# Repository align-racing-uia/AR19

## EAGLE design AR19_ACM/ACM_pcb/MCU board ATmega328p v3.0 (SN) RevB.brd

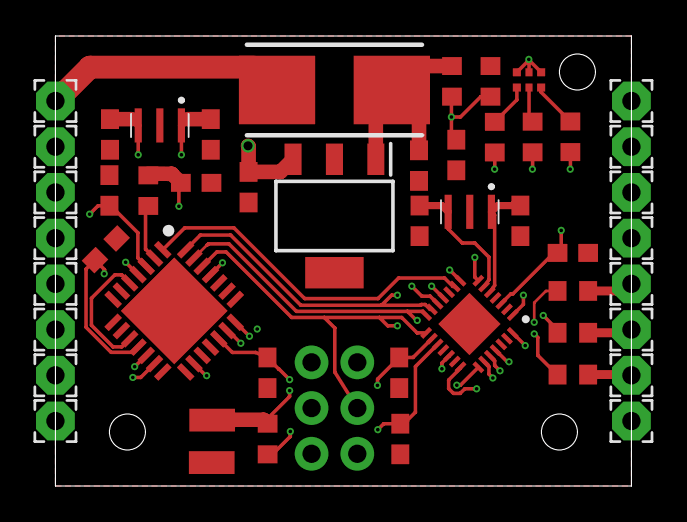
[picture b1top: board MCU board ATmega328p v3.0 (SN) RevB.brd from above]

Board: 4 copper layers, 32.0 x 25.0 mm, 50 parts (0 on the bottom side), 35 nets.

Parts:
5V: 5V_V5; 2,15/1,0
5V1: 5V_H0; 2,15/1,0
12V: 12V_V7; 2,15/1,0
C1, C6, C7, C8, C12, C13, C16, C17: 0.1uF; C0603
C2, C3, C5, C9: 22pF; C0603
C10, C11: 10uF; C0603
CANH: I/O_CANH_V3; 2,15/1,0
CANL: I/O_CANH_V4; 2,15/1,0
FUSE: 0154005.DRT; 0154001.DRT
GND: GND_V6; 2,15/1,0
GND30: GND_V0; 2,15/1,0
I/O_AD0: I/O_AD0_H7; 2,15/1,0
I/O_AD1: I/O_AD1_H6; 2,15/1,0
I/O_ADC2_SDA: I/O_ADC2_SDA_H5; 2,15/1,0
I/O_ADC3_SCL: I/O_ADC3_SCL_H4; 2,15/1,0
IC1: ATMEGA328P-MMH; QFN45P400X400X100-29N
IC2: MIC5239-5.0YS_TR; SOT230P700X170-4N
IC3: MCP25625-E_ML; QFN65P600X600X100-29N
J1: AVR_SPI_PROG_3X2NS; 2X3-NS
LED1: SMLP36RGB2W3R; ROHM-1510-(0604)
MISO: MISO_H3; 2,15/1,0
MOSI: MOSI__H2; 2,15/1,0
PWM0: PWM0_V2; 2,15/1,0
PWM1_INT1: PWM0_INT_V1; 2,15/1,0
R1, R3: 10kOhm; R0603
R2, R6, R7, R8: 200Ohm; R0603
R4: 290Ohm; R0603
R5: 190Ohm; R0603
R9: 3kOhm; R0603
R10: 2kOhm; R0603
RES_PAD1: RES_PAD; SMD1,27-2,54
RES_PAD2: RES_PAD2; SMD1,27-2,54
SCK: SCK_H1; 2,15/1,0
U1, U2: CSTNE16M0V530000R0

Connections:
5V: 5V.1, 5V1.1, C6.1, C7.1, C8.1, C11.1, C12.1, C13.1, C16.1, C17.1, IC1.3, IC1.16, IC1.17, IC2.3, IC3.3, IC3.11, IC3.19, J1.2, LED1.4, LED1.5, LED1.6, R1.1, R3.2
12V_FUSED: C10.1, FUSE.2, IC2.1, R9.2
12V_UNFUSED: 12V.1, FUSE.1
BLUE_LED: IC1.11, R5.1
CANH: CANH.1, IC3.13
CANL: CANL.1, IC3.12
CAN_CS: IC1.9, IC3.1
CAN_INT: IC1.28, IC3.25
CAN_OSC1: C5.1, IC3.21, U1.1
CAN_OSC2: C2.1, IC3.20, U1.3
GND: C1.2, C2.2, C3.2, C5.2, C6.2, C7.2, C8.2, C9.2, C10.2, C11.2, C12.2, C13.2, C16.2, C17.2, GND.1, GND30.1, IC1.4, IC1.18, IC1.29, IC2.2, IC2.4, IC3.14, IC3.15, IC3.17, IC3.18, IC3.22, IC3.29, J1.6, R10.1, RES_PAD2.1, U1.2, U2.2
GREEN_LED: IC1.8, R2.1
I/OAD0: I/O_AD0.1, IC1.22
I/OADC2: I/O_ADC2_SDA.1, IC1.23
I/O_ADC3: I/O_ADC3_SCL.1, IC1.24
I/O_D2_INT: IC1.1, PWM1_INT1.1
MCU_OSC1: C3.1, IC1.5, U2.1
MCU_OSC2: C9.1, IC1.6, U2.3
MISO: IC1.14, IC3.27, J1.1, R7.1
MOSI: IC1.13, IC3.28, J1.4, R8.1
unnamed: IC3.2, R1.2
unnamed: IC1.12, PWM0.1
unnamed: I/O_AD1.1, IC1.21
unnamed: LED1.1, R2.2
unnamed: LED1.2, R4.2
unnamed: LED1.3, R5.2
unnamed: R6.2, SCK.1
unnamed: MISO.1, R7.2
unnamed: MOSI.1, R8.2
RED_LED: IC1.7, R4.1
RESET_MCU: IC1.25, J1.5, R3.1, RES_PAD1.1
RXCAN: IC3.5, IC3.10
SCK: IC1.15, IC3.26, J1.3, R6.1
TXCAN: IC3.4, IC3.16
VOLTAGE_CHECK: C1.1, IC1.19, R9.1, R10.2

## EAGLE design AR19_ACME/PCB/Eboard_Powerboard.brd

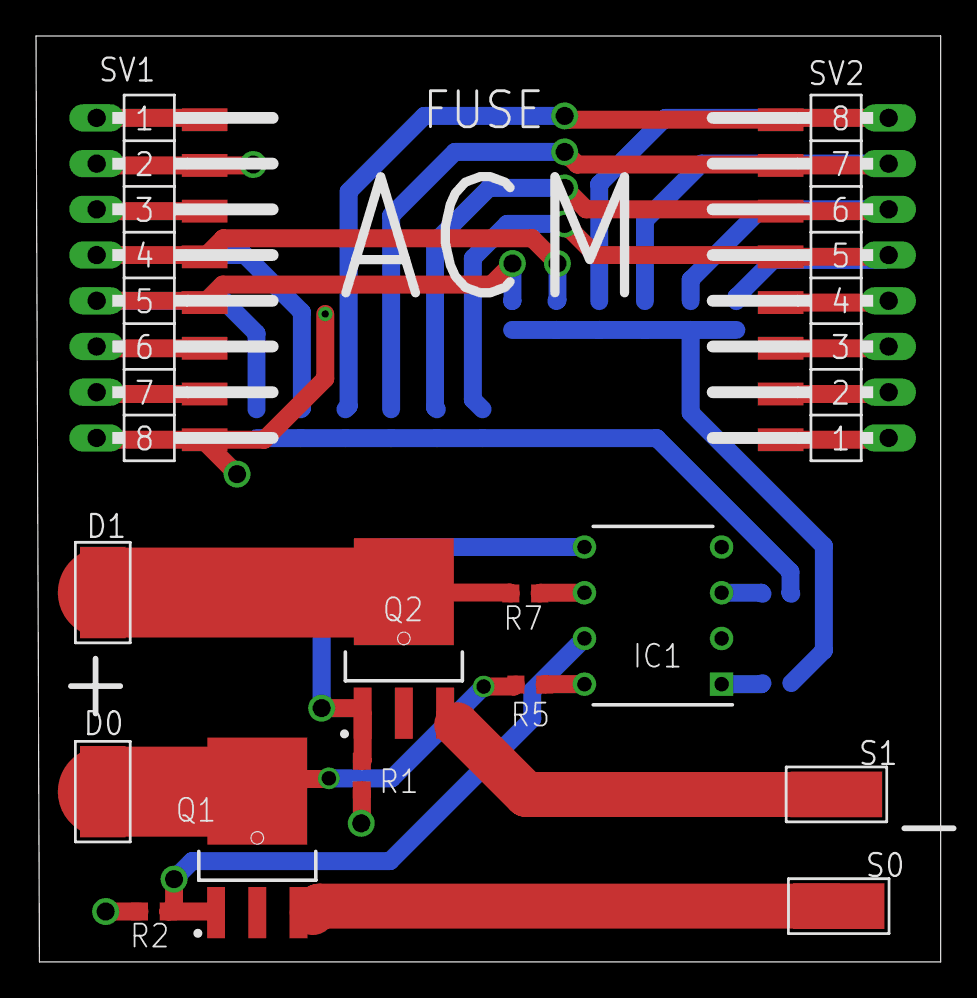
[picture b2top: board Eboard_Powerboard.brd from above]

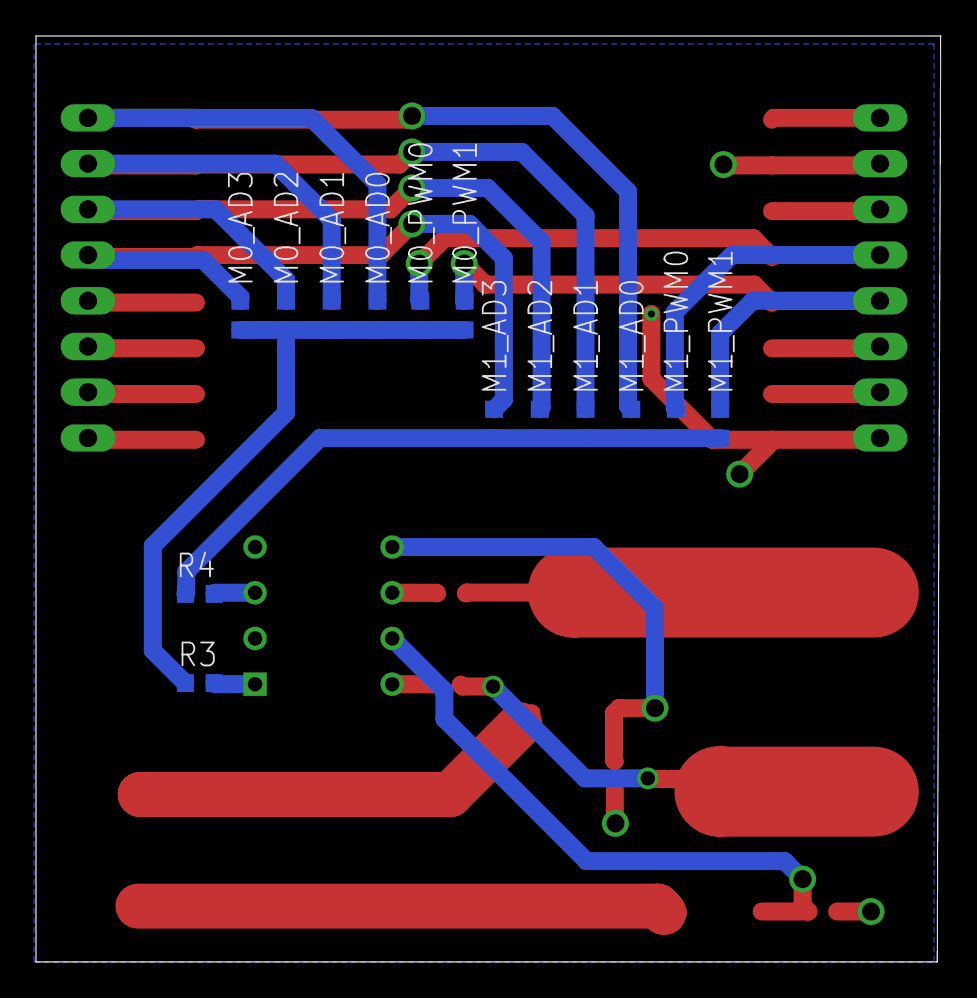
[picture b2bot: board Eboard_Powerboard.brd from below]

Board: 2 copper layers, 50.3 x 51.4 mm, 28 parts (14 on the bottom side), 27 nets.

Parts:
D0, D1: 5-2,5
IC1: Optocoupler DIP; DIP762W60P254L966H485Q8N
M0_AD0, M0_AD1, M0_AD2, M0_AD3, M0_PWM0, M0_PWM1, M1_AD0, M1_AD1, M1_AD2, M1_AD3, M1_PWM0, M1_PWM1: RESC1608X55N
Q1, Q2: TO229P990X238-4N
R1, R2: RESC1608X55N
R3, R4: 200 Ohm; RESC1608X55N
R5, R7: 1K Ohm; RESC1608X55N
S0, S1: 5-2,5
SV1, SV2: MA08-1W
U$1: ACM_CASTELLATED; ACM_CAS_FP

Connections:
AD0: M0_AD0.2, M1_AD0.2, SV2.8, U$1.I/O_AD0
AD1: M0_AD1.2, M1_AD1.2, SV2.7, U$1.I/O_AD1
AD2: M0_AD2.2, M1_AD2.2, SV2.6, U$1.I/O_AD2_SDA
AD3: M0_AD3.2, M1_AD3.2, SV2.5, U$1.I/O_AD3_SCL
DRAIN0: D0.1, Q1.4, R5.2
DRAIN1: D1.1, Q2.4, R7.2
GATE0: IC1.7, Q1.1, R2.1
GATE1: IC1.5, Q2.1, R1.1
GND: IC1.2, IC1.4, R1.2, R2.2, SV1.2, SV1.8, U$1.GND, U$1.GND30
unnamed: SV1.3, U$1.5V
unnamed: IC1.1, R3.1
unnamed: SV1.1, U$1.12V
unnamed: SV1.6, U$1.CANL
unnamed: SV1.7, U$1.CANH
unnamed: IC1.3, R4.1
unnamed: IC1.8, R5.1
unnamed: SV2.4, U$1.MISO
unnamed: SV2.3, U$1.MOSI
unnamed: SV2.2, U$1.SCK
unnamed: SV2.1, U$1.5V1
unnamed: IC1.6, R7.1
unnamed: M0_AD0.1, M0_AD1.1, M0_AD2.1, M0_AD3.1, M0_PWM0.1, M0_PWM1.1, R3.2
unnamed: M1_AD0.1, M1_AD1.1, M1_AD2.1, M1_AD3.1, M1_PWM0.1, M1_PWM1.1, R4.2
PWM0: M0_PWM0.2, M1_PWM0.2, SV1.4, U$1.PWM0
PWM1: M0_PWM1.2, M1_PWM1.2, SV1.5, U$1.PWM1_INT1
SOURCE0: Q1.3, S0.1
SOURCE1: Q2.3, S1.1

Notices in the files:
parts and their libraries:
SparkFun-Connectors: Licensing: Creative Commons ShareAlike 4.0 International - https://creativecommons.org/licenses/by-sa/4.0
